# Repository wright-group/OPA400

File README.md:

# OPA400
Designs for an Optical Parametric Amplifier pumped with 400 nm light

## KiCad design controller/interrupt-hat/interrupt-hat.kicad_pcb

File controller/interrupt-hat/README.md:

# interrupt-hat

A Raspberry Pi hat to connect GPIO to powered interrupts with onboard indicators.

## PCB

This PCB was designed using KiCAD version 5.
Refer to `interrupt-hat.pdf` for schematic.
PCB images generated with [tracespace](https://github.com/tracespace/tracespace) follow.

Bill of Materials

| reference      | value          | manufacturer | part number          | vendors |
| :------------- | :------------- | :----------- | :------------------- | :------ |

## Changelog

### Revision A

#### Added
- initial design

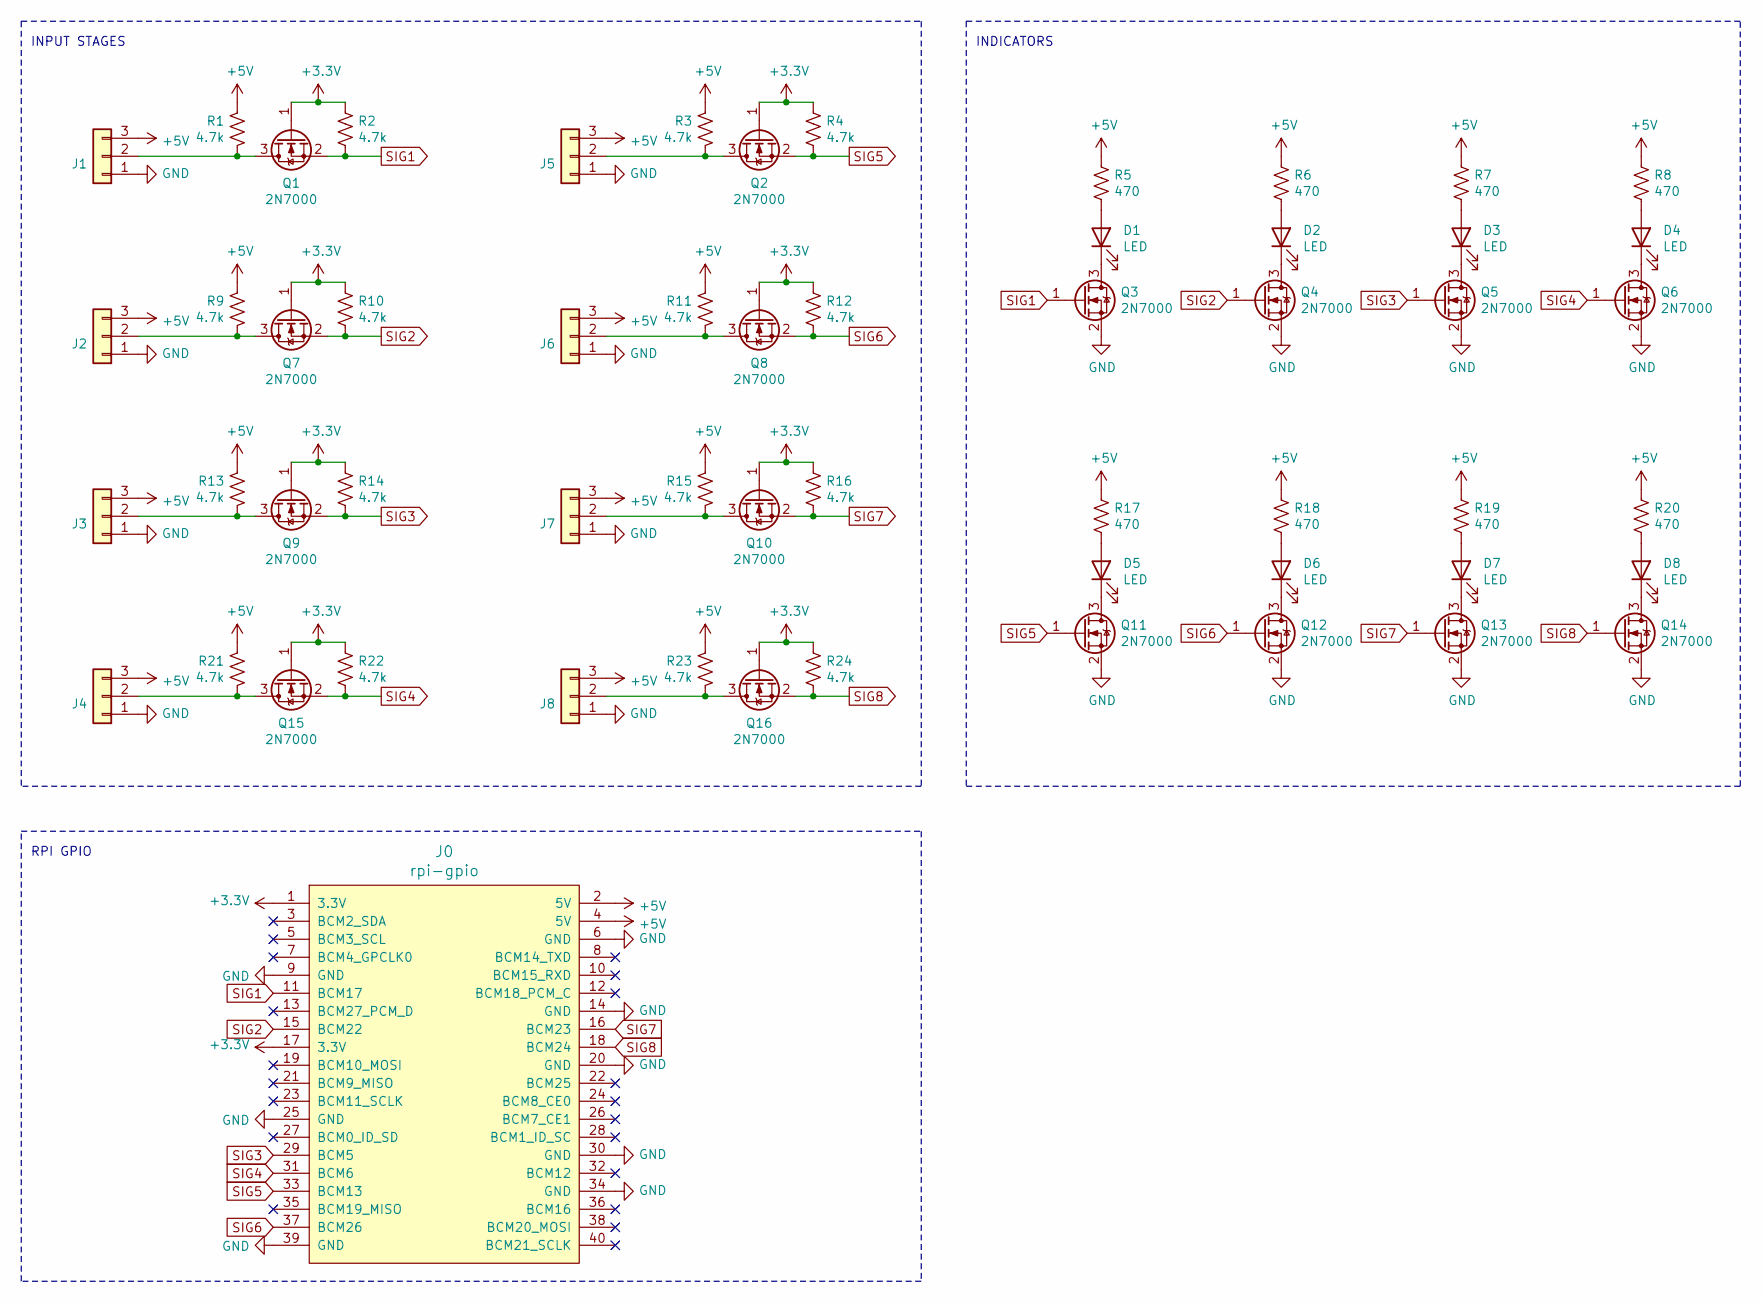
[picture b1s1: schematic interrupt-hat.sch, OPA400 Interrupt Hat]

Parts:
D1, D2, D3, D4, D5, D6, D7, D8: LED; LED_1206_3216Metric_Pad1.42x1.75mm_HandSolder
J0: rpi-gpio; rpi-header
J1, J2, J3, J4, J5, J6, J7, J8: Conn_01x03; 0022124032
Q1, Q2, Q3, Q4, Q5, Q6, Q7, Q8, Q9, Q10, Q11, Q12, Q13, Q14, Q15, Q16: 2N7000; TSOT-23
R1, R2, R3, R4, R9, R10, R11, R12, R13, R14, R15, R16, R21, R22, R23, R24: 4.7k; R_1206_3216Metric_Pad1.30x1.75mm_HandSolder
R5, R6, R7, R8, R17, R18, R19, R20: 470; R_1206_3216Metric_Pad1.30x1.75mm_HandSolder

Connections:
+3V3: J0.1 (3.3V), J0.17 (3.3V), Q1.1 (G), Q2.1 (G), Q7.1 (G), Q8.1 (G), Q9.1 (G), Q10.1 (G), Q15.1 (G), Q16.1 (G), R2.1, R4.1, R10.1, R12.1, R14.1, R16.1, R22.1, R24.1
+5V: J0.2 (5V), J0.4 (5V), J1.3, J2.3, J3.3, J4.3, J5.3, J6.3, J7.3, J8.3, R1.2, R3.2, R5.1, R6.1, R7.1, R8.1, R9.2, R11.2, R13.2, R15.2, R17.1, R18.1, R19.1, R20.1, R21.2, R23.2
GND: J0.6 (GND), J0.9 (GND), J0.14 (GND), J0.20 (GND), J0.25 (GND), J0.30 (GND), J0.34 (GND), J0.39 (GND), J1.1, J2.1, J3.1, J4.1, J5.1, J6.1, J7.1, J8.1, Q3.2 (S), Q4.2 (S), Q5.2 (S), Q6.2 (S), Q11.2 (S), Q12.2 (S), Q13.2 (S), Q14.2 (S)
unnamed: D1.1 (K), Q3.3 (D)
unnamed: D1.2 (A), R5.2
unnamed: D2.1 (K), Q4.3 (D)
unnamed: D2.2 (A), R6.2
unnamed: D3.1 (K), Q5.3 (D)
unnamed: D3.2 (A), R7.2
unnamed: D4.1 (K), Q6.3 (D)
unnamed: D4.2 (A), R8.2
unnamed: D5.1 (K), Q11.3 (D)
unnamed: D5.2 (A), R17.2
unnamed: D6.1 (K), Q12.3 (D)
unnamed: D6.2 (A), R18.2
unnamed: D7.1 (K), Q13.3 (D)
unnamed: D7.2 (A), R19.2
unnamed: D8.1 (K), Q14.3 (D)
unnamed: D8.2 (A), R20.2
unnamed: J1.2, Q1.3 (D), R1.1
unnamed: J2.2, Q7.3 (D), R9.1
unnamed: J3.2, Q9.3 (D), R13.1
unnamed: J4.2, Q15.3 (D), R21.1
unnamed: J5.2, Q2.3 (D), R3.1
unnamed: J6.2, Q8.3 (D), R11.1
unnamed: J7.2, Q10.3 (D), R15.1
unnamed: J8.2, Q16.3 (D), R23.1
SIG1: J0.11 (BCM17), Q1.2 (S), Q3.1 (G), R2.2
SIG2: J0.15 (BCM22), Q4.1 (G), Q7.2 (S), R10.2
SIG3: J0.29 (BCM5), Q5.1 (G), Q9.2 (S), R14.2
SIG4: J0.31 (BCM6), Q6.1 (G), Q15.2 (S), R22.2
SIG5: J0.33 (BCM13), Q2.2 (S), Q11.1 (G), R4.2
SIG6: J0.37 (BCM26), Q8.2 (S), Q12.1 (G), R12.2
SIG7: J0.16 (BCM23), Q10.2 (S), Q13.1 (G), R16.2
SIG8: J0.18 (BCM24), Q14.1 (G), Q16.2 (S), R24.2

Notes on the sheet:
INPUT STAGES
INDICATORS
RPI GPIO

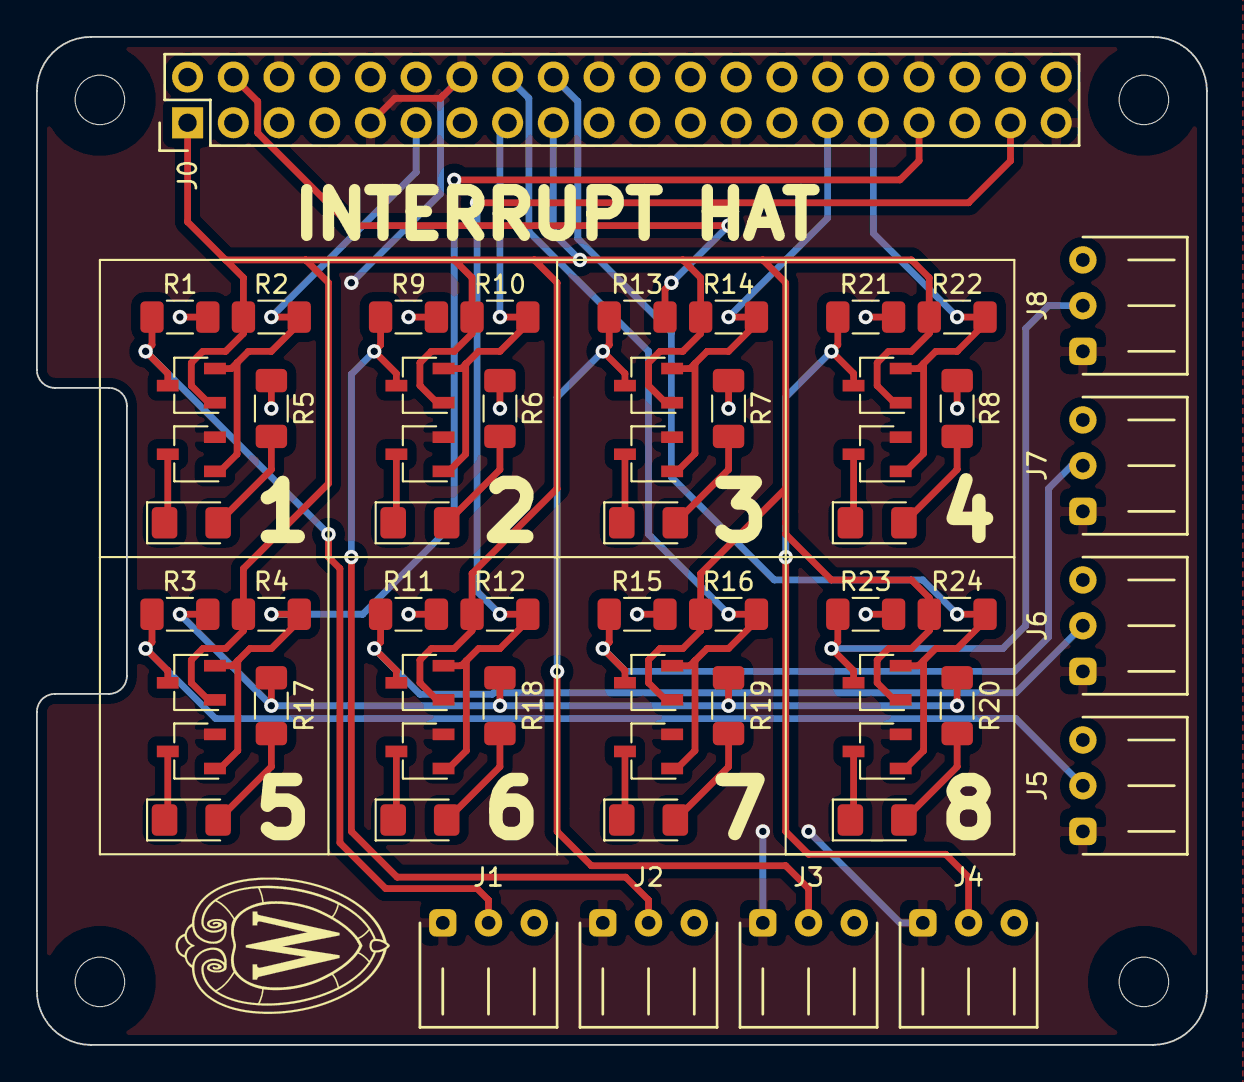
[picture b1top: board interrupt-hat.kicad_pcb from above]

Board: 2 copper layers, 65.0 x 56.0 mm, 57 parts (0 on the bottom side), 35 nets.

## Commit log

2020-02-07 Add linear stage parts
2020-02-14 Parameterize height of DE-9 Housing
2020-02-14 update stl for changed de9 housing
2020-02-29 Modelling the box
2020-03-03 Add holes for component mounting
2020-03-05 Simplify top of box, add group logo
2020-03-12 Extract out pieces into independent files
2021-02-15 refactor repository
2021-02-16 initial interrupt hat design
2021-04-28 controller readme
2022-03-28 Rework for not mounting motor itself, only connector and sensor
